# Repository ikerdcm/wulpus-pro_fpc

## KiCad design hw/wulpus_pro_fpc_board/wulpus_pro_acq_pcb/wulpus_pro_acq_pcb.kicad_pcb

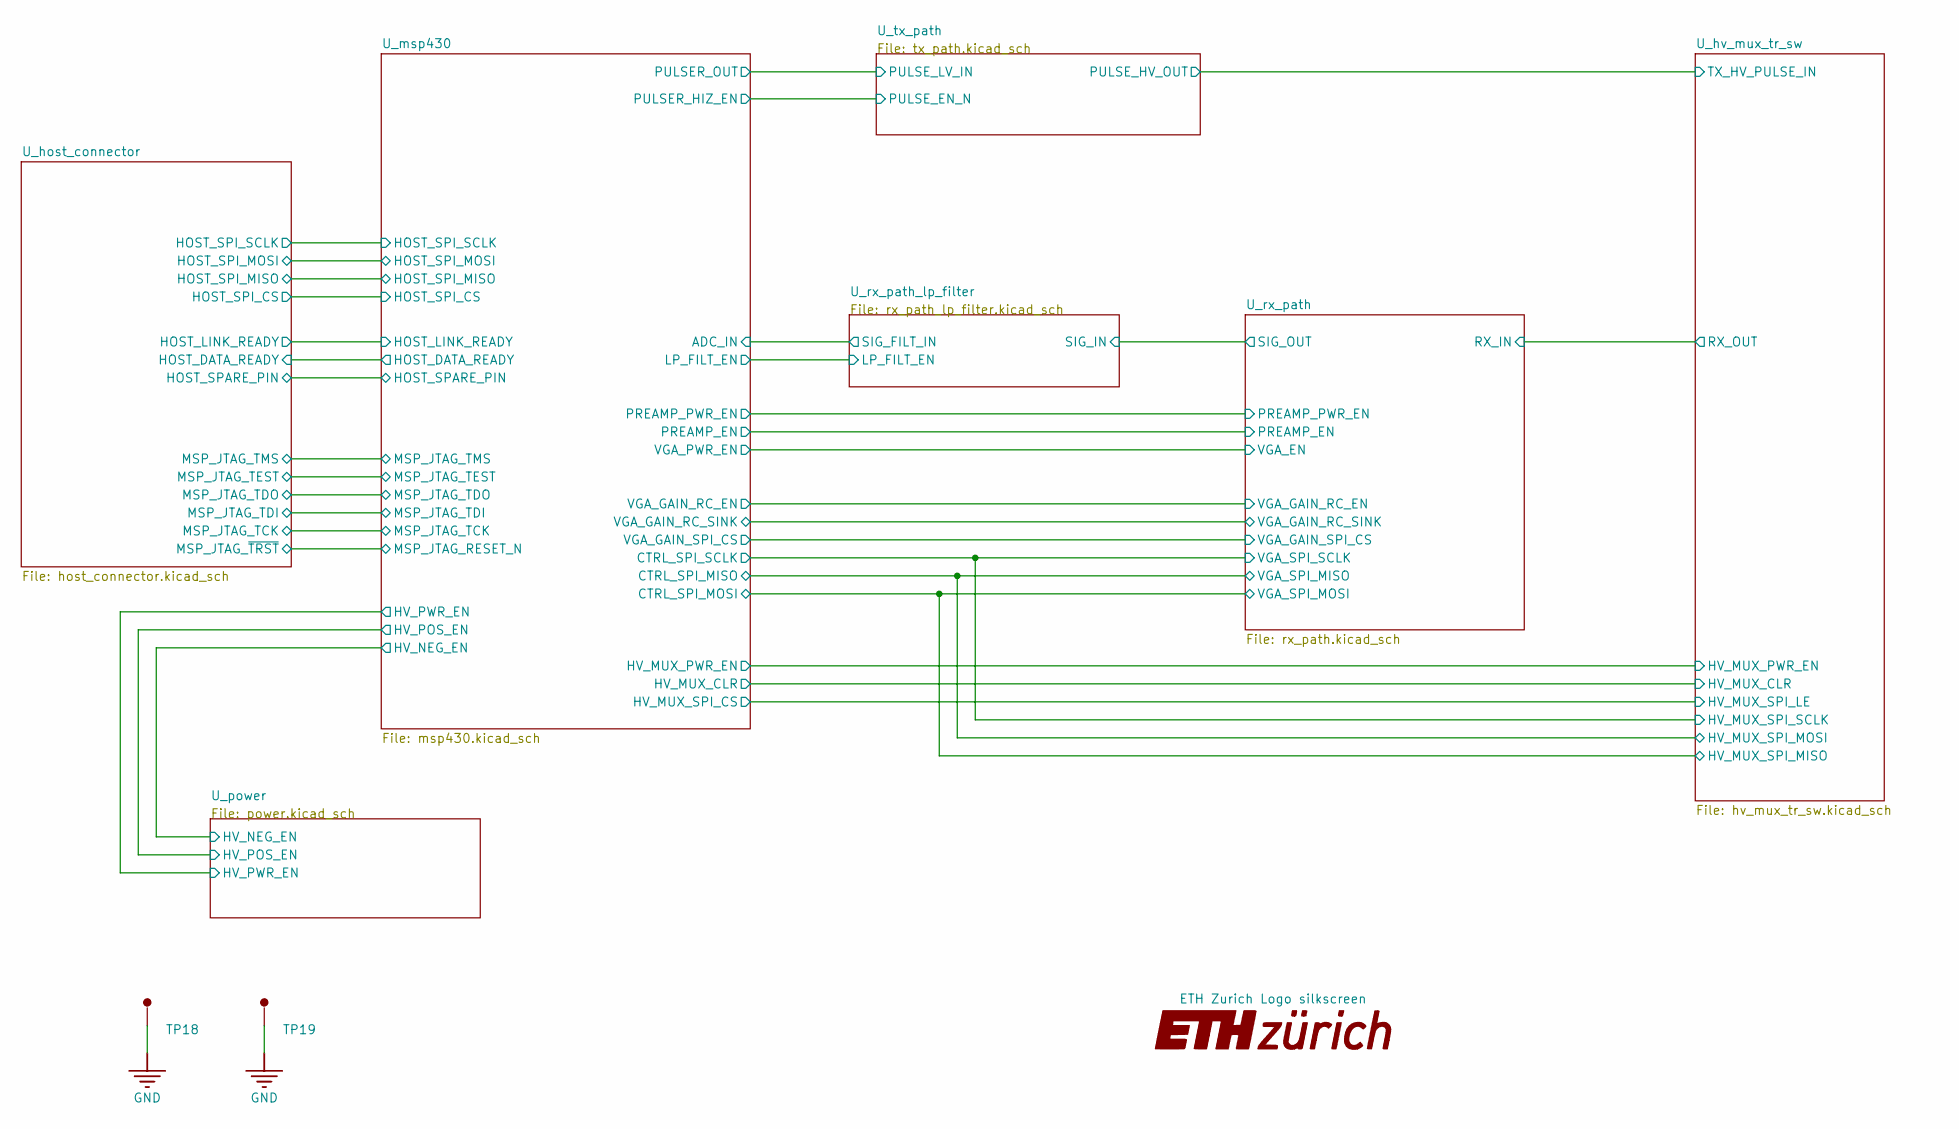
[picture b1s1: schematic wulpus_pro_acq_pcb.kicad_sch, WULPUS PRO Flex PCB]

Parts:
ART1: ETH Zurich Logo silkscreen; ETH_zurich_2mm
TP18, TP19: TP-SM-C-100; TestPoint_Pad_D1.0mm

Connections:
GND: TP18.1 (1_1), TP19.1 (1_1); also elsewhere on the board

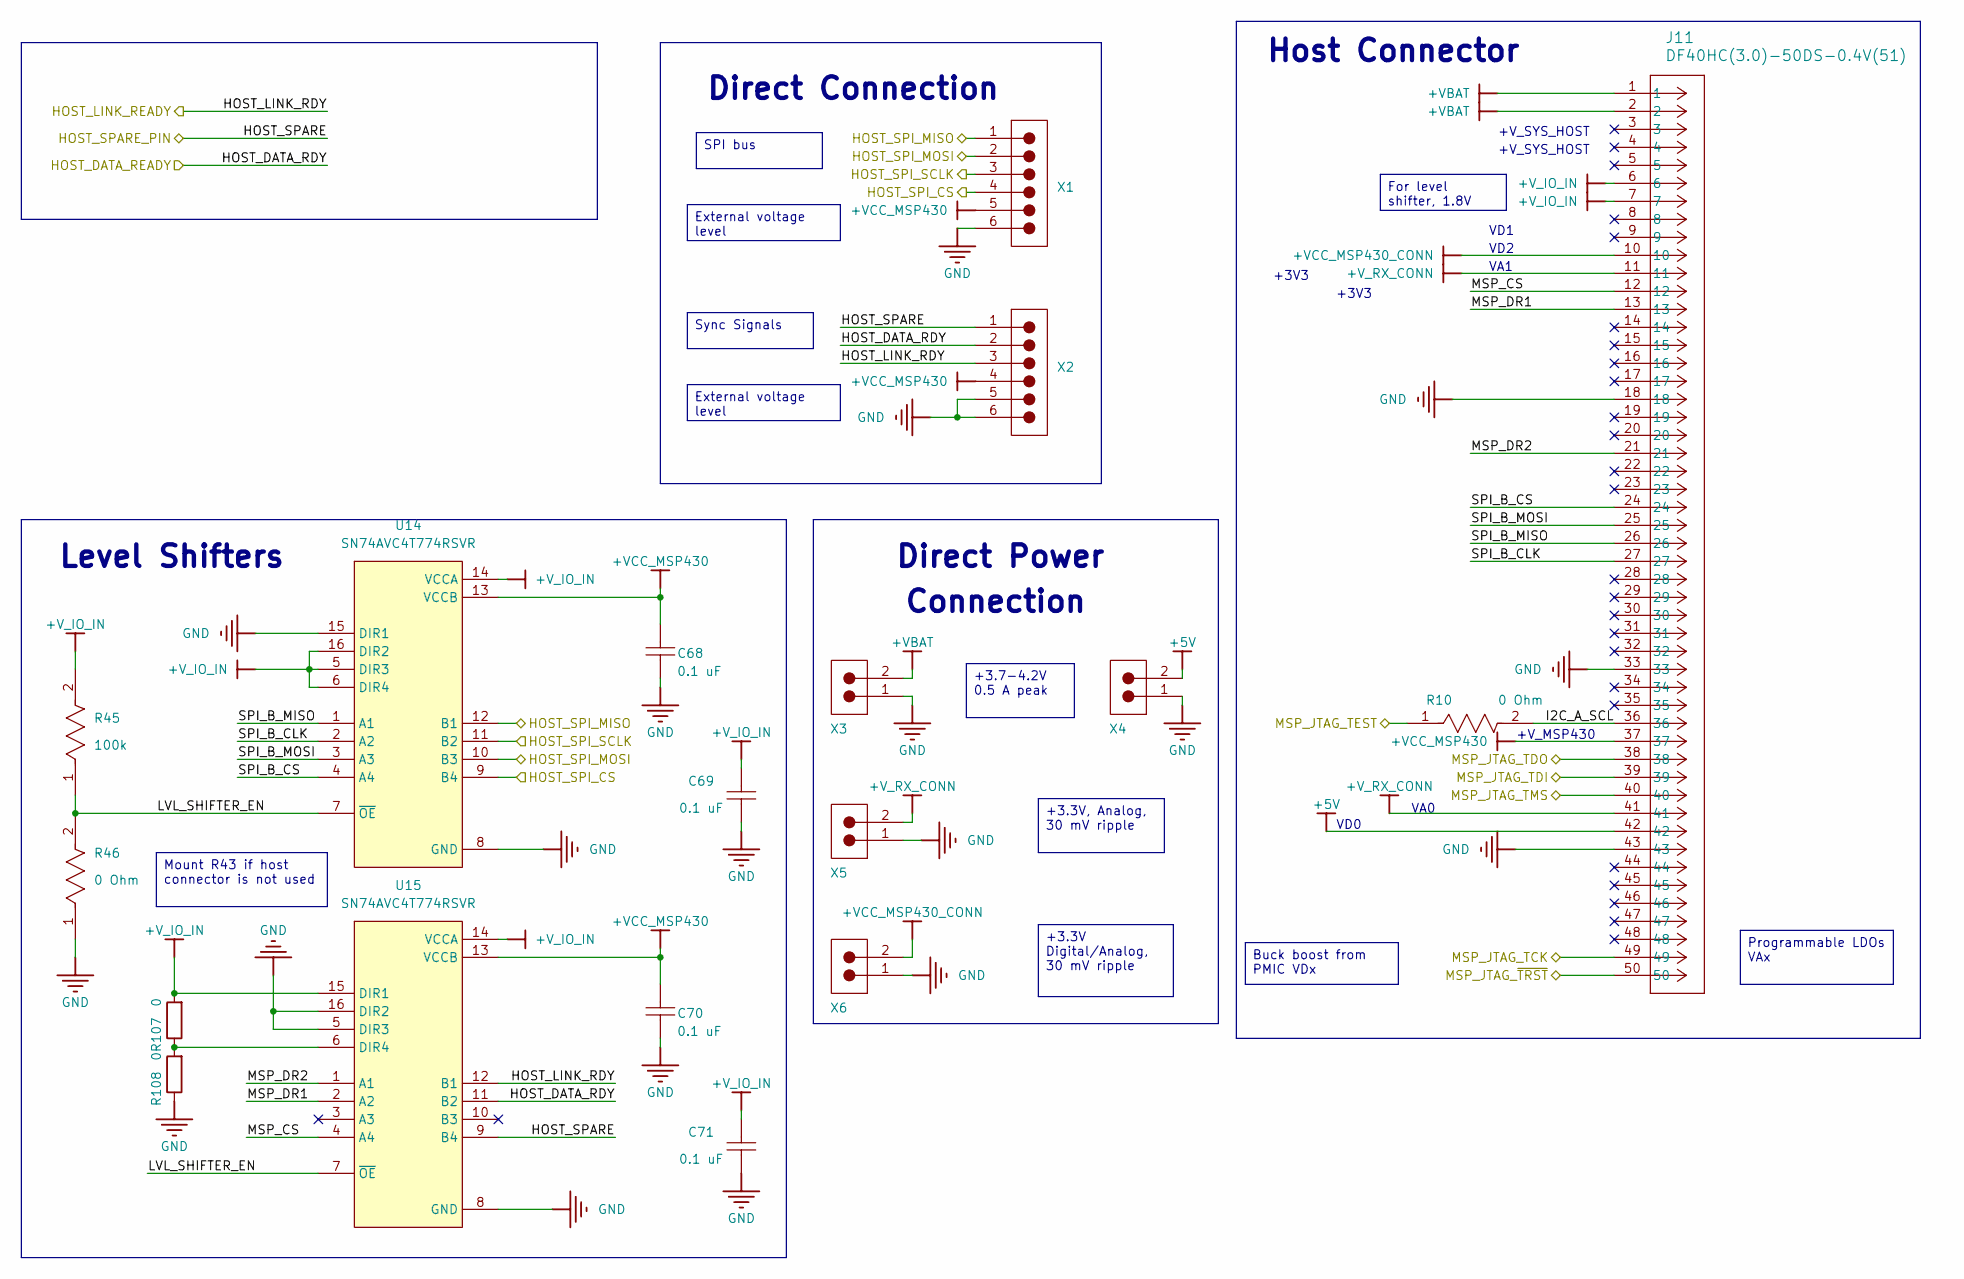
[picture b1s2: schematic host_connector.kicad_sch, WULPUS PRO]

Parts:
C68, C69, C70, C71: 0.1 uF; C_0402_1005Metric; PART NUMBER C0402C104K4RACTU
J11: DF40HC(3.0)-50DS-0.4V(51); CONN_DF40HC3.0-50DS-0.4V51_HIR; MPN DF40HC(3.0)-50DS-0.4V(51); LCSC C3652838
R10, R46: 0 Ohm; R_0402_1005Metric; TOLERANCE 5%; VOLTAGE RATING 50V; MPN CRCW04020000Z0ED
R45: 100k; R_0402_1005Metric; VOLTAGE RATING (DC) 50V; TOLERANCE 1%; MPN ERJ-2RKF1003X
R107, R108: 0; R_0402_1005Metric; Tolerance 5%; MPN ERJ-2GE0R00X; LCSC C17168
U14, U15: SN74AVC4T774RSVR; UQFN-16_1.8x2.6mm_P0.4mm; MPN SN74AVC4T774RSVR; DIGI-KEY_PART_NUMBER 296-24741-1-ND
X1, X2: 68000-106HLF; PinHeader_1x06_P2.54mm_Vertical; CURRENT RATING 3A; VOLTAGE RATING 1.5kV; MPN 68000-102HLF
X3, X4, X5, X6: 68000-102HLF; PinHeader_1x02_P2.54mm_Vertical; CURRENT RATING 3A; FLAMMABILITY RATING UL94 V-0; MANUFACTURER PART NUMBER 68000-102HLF

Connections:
+5V: J11.42, X4.2; also elsewhere on the board
+VBAT: J11.1, J11.2, X3.2; also elsewhere on the board
+VBAT_STM: C68.1, C70.1, J11.37, U14.13 (VCCB), U15.13 (VCCB), X1.5, X2.4; also elsewhere on the board
+VCC_MSP430_CONN: J11.10, X6.2; also elsewhere on the board
+V_IO_IN: C69.1, C71.1, J11.6, J11.7, R45.2, R107.2, U14.5 (DIR3), U14.6 (DIR4), U14.14 (VCCA), U14.16 (DIR2), U15.14 (VCCA), U15.15 (DIR1)
+V_RX_CONN: J11.11, J11.41, X5.2; also elsewhere on the board
/U_host_connector/HOST_DATA_RDY: U15.11 (B2), X2.2; also elsewhere on the board
/U_host_connector/HOST_LINK_RDY: U15.12 (B1), X2.3; also elsewhere on the board
/U_host_connector/HOST_SPARE: U15.9 (B4), X2.1; also elsewhere on the board
/U_host_connector/HOST_SPI_CS: U14.9 (B4), X1.4; also elsewhere on the board
/U_host_connector/HOST_SPI_MISO: U14.12 (B1), X1.1; also elsewhere on the board
/U_host_connector/HOST_SPI_MOSI: U14.10 (B3), X1.2; also elsewhere on the board
/U_host_connector/HOST_SPI_SCLK: U14.11 (B2), X1.3; also elsewhere on the board
/U_host_connector/I2C_A_SCL: J11.36, R10.2
/U_host_connector/LVL_SHIFTER_EN: R45.1, R46.2, U14.7 (~OE), U15.7 (~OE)
/U_host_connector/MSP_CS: J11.12, U15.4 (A4)
/U_host_connector/MSP_DR1: J11.13, U15.2 (A2)
/U_host_connector/MSP_DR2: J11.21, U15.1 (A1)
/U_host_connector/SPI_B_CLK: J11.27, U14.2 (A2)
/U_host_connector/SPI_B_CS: J11.24, U14.4 (A4)
/U_host_connector/SPI_B_MISO: J11.26, U14.1 (A1)
/U_host_connector/SPI_B_MOSI: J11.25, U14.3 (A3)
/U_msp430/MSP_JTAG_RESET_N: J11.50; also elsewhere on the board
/U_msp430/MSP_JTAG_TCK: J11.49; also elsewhere on the board
/U_msp430/MSP_JTAG_TDI: J11.39; also elsewhere on the board
/U_msp430/MSP_JTAG_TDO: J11.38; also elsewhere on the board
/U_msp430/MSP_JTAG_TEST: R10.1; also elsewhere on the board
/U_msp430/MSP_JTAG_TMS: J11.40; also elsewhere on the board
GND: C68.2, C69.2, C70.2, C71.2, J11.18, J11.33, J11.43, R46.1, R108.1, U14.8 (GND), U14.15 (DIR1), U15.5 (DIR3), U15.8 (GND), U15.16 (DIR2), X1.6, X2.5, X2.6, X3.1, X4.1, X5.1, X6.1; also elsewhere on the board
unnamed: R107.1, R108.2, U15.6 (DIR4)

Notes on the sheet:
+V_SYS_HOST
Connection
Direct Connection
Direct Power
VD1
+V_MSP430
+3V3
Level Shifters
VA1
VD0
VD2
Host Connector
VA0
+3.3V Digital/Analog, 30 mV ripple
Mount R43 if host connector is not used
+3.3V, Analog, 30 mV ripple
Sync Signals
SPI bus
+3.7-4.2V 0.5 A peak
External voltage level
For level shifter, 1.8V
Programmable LDOs VAx
Buck boost from PMIC VDx

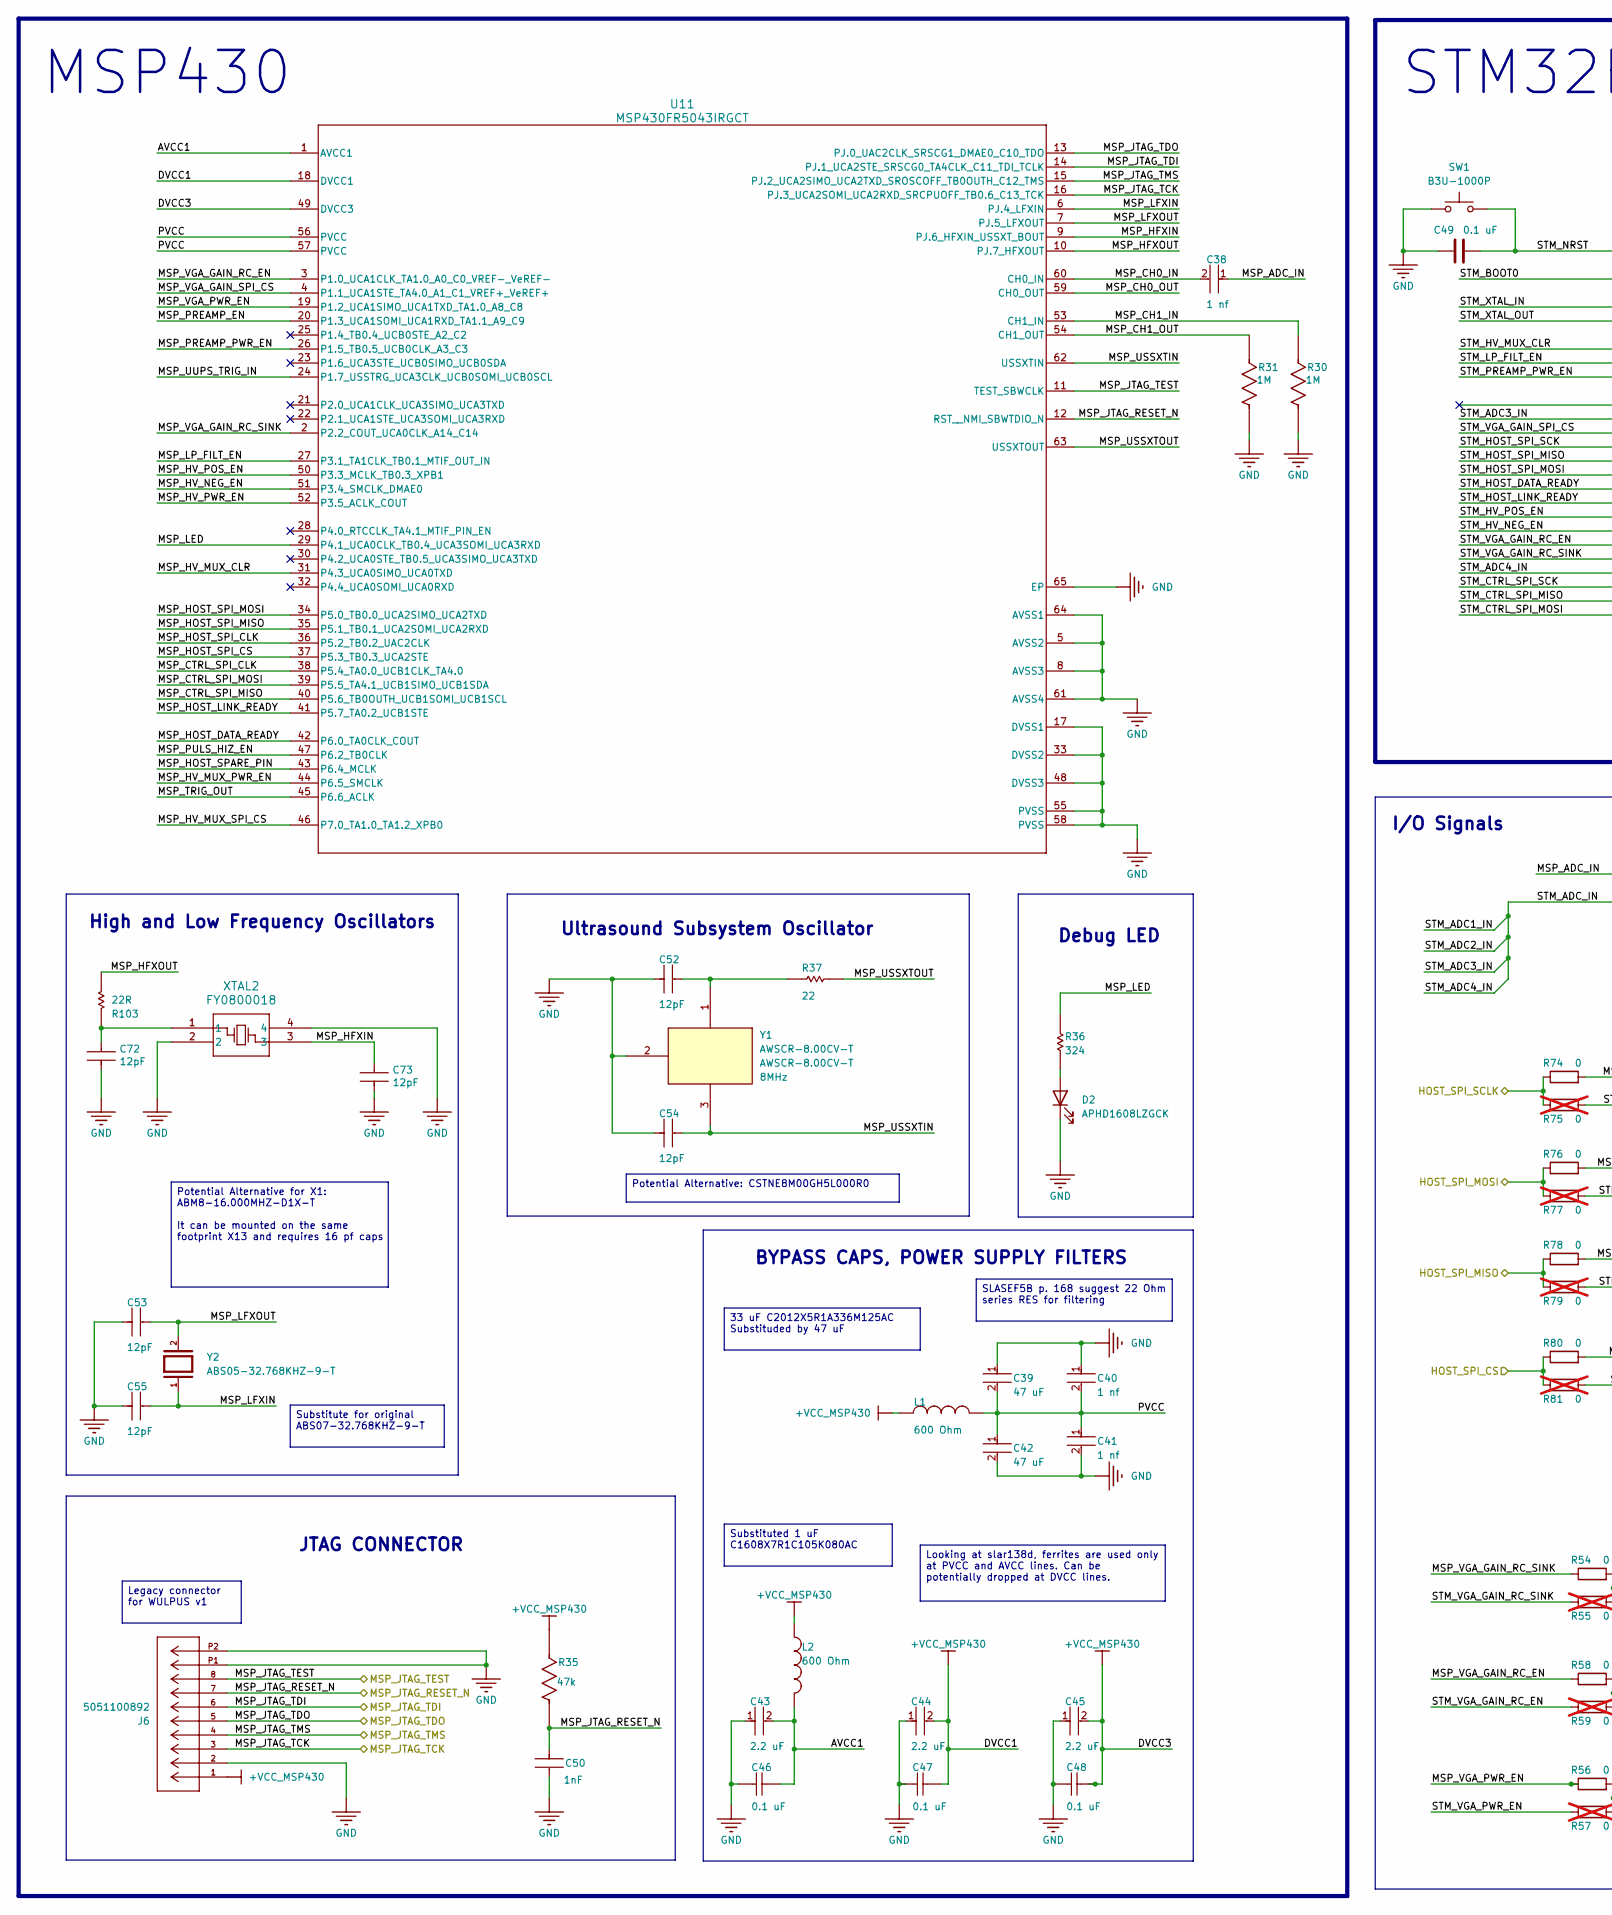
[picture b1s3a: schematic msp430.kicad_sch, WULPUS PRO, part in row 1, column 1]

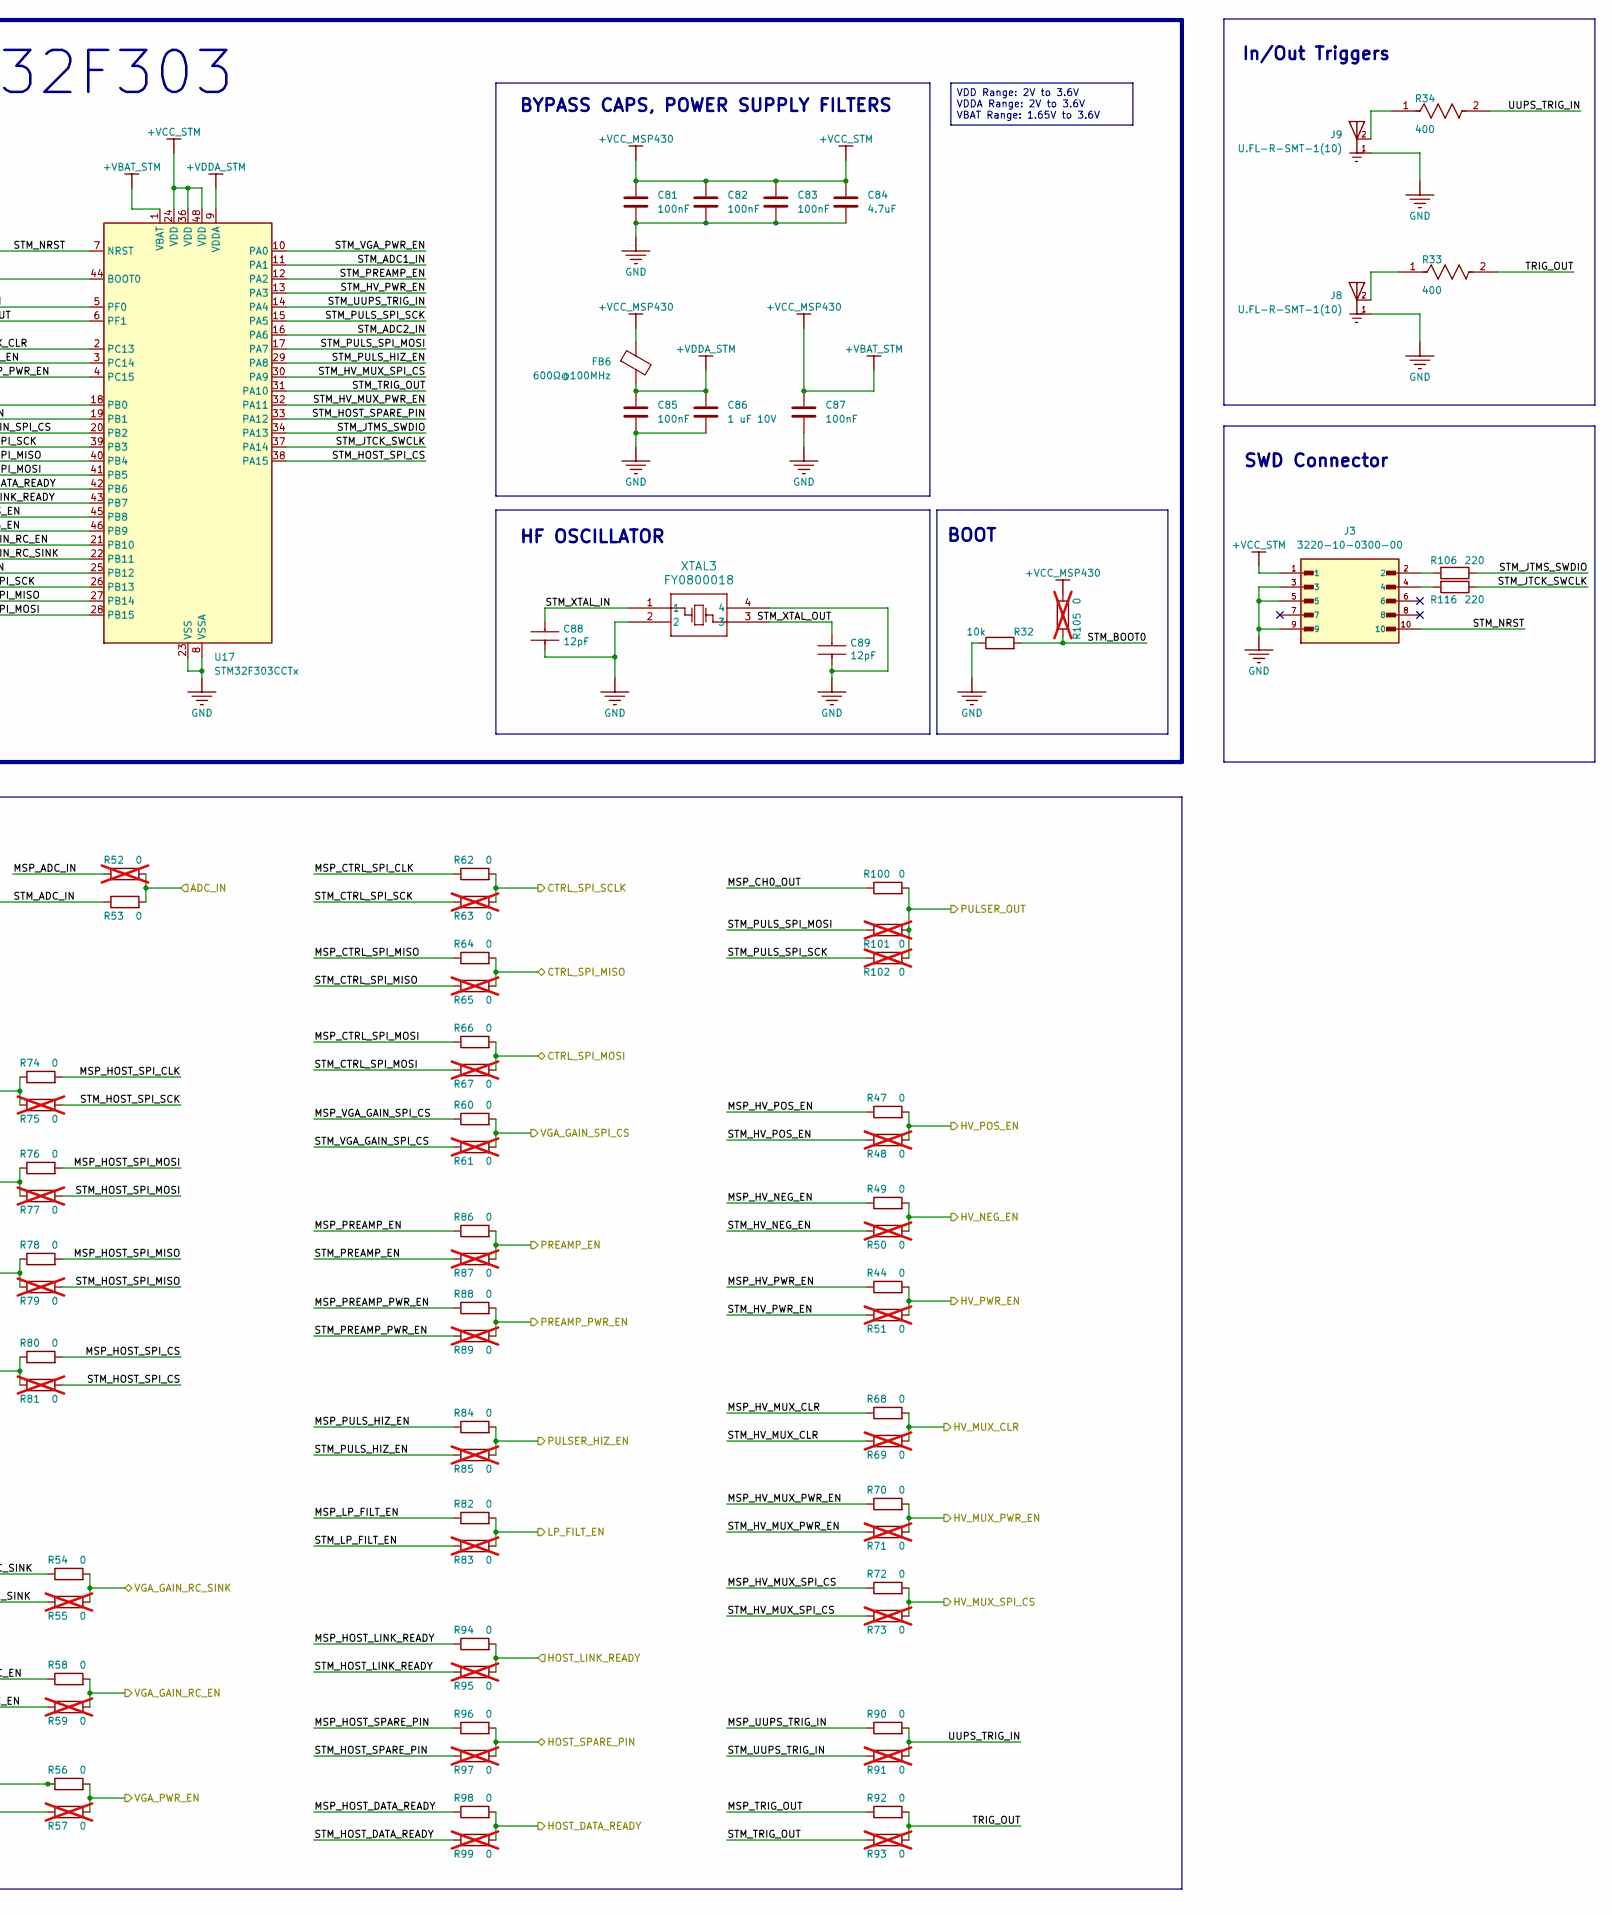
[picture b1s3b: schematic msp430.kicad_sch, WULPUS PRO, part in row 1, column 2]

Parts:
C38, C40, C41: 1 nf; C_0402_1005Metric; TOLERANCE 5%; VOLTAGE RATING 50V; PART NUMBER GRM1555C1H102JA01D
C39, C42: 47 uF; C_0603_1608Metric; TOLERANCE 20%; VOLTAGE RATING (DC) 6.3V; PART NUMBER GRM188R60J476ME01D
C43, C44, C45: 2.2 uF; C_0402_1005Metric; VOLTAGE RATING 10V; VOLTAGE RATING (DC) 10V; PART NUMBER C1005X7S1A225K050BC
C46, C47, C48: 0.1 uF; C_0402_1005Metric; PART NUMBER C0402C104K4RACTU
C49: 0.1 uF; C_0402_1005Metric; MPN C0402C104K4RACTU
C50: 1000 pF 50V; C_0402_1005Metric; TOLERANCE 5%; VOLTAGE RATING 50V; PART NUMBER GRM1555C1H102JA01D
C52, C53, C54, C55, C72, C73, C88, C89: 12 pF 50V; C_0402_1005Metric; TOLERANCE 2%; VOLTAGE RATING 50V; PART NUMBER GJM1555C1H120GB01D
C81, C82, C83, C85, C87: 100nF; C_0402_1005Metric; MPN C0402C104K4RACTU
C84: 4.7uF; C_0402_1005Metric; MPN MLASL105BB5475MFNB33
C86: 1 uF 10V; C_0402_1005Metric; MPN GRM155Z71A105KE01D
D2: APHD1608LZGCK; LED_0603_1608Metric; MPN APHD1608LZGCK
FB6: 600Ω@100MHz; L_0603_1608Metric; MPN BLM18AG601SZ1; LCSC C710353
J3: 3220-10-0300-00; CNC_3220-10-0300-00; PARTREV D; LCSC C7501307
J6: 5051100892; CON_5051100892_MOL; MPN 5051100892; LCSC C5902847
J8, J9: U.FL-R-SMT-1(10); HRS_U.FL-R-SMT-1_10_; MPN U.FL-R-SMT-1(10); DigiKey_Part_Number H11891CT-ND
L1, L2: 742792040; L_0805_2012Metric_Pad1.05x1.20mm_HandSolder; MPN 742792040
R30, R31: CRCW04021M00FKED; R_0402_1005Metric; POWER RATING 63mW; VOLTAGE RATING (DC) 50V; MPN CRCW04021M00FKED
R32: 10k; R_0402_1005Metric
R33, R34: 400; R_0402_1005Metric; TOLERANCE 1%; VOLTAGE RATING 50V; MPN CRCW04021R00FKEDC
R35: CRCW040247K0FKED; R_0402_1005Metric; TOLERANCE 1%; VOLTAGE RATING (DC) 50V; MPN CRCW040247K0FKED
R36: 324R; R_0402_1005Metric; PART NUMBER CPF0402B324RE1
R37, R103: 22R; R_0402_1005Metric; PART NUMBER RC0402JR-0722RL
R44, R47, R49, R53, R54, R56, R58, R60, R62, R64, R66, R68, R70, R72, R74, R76, R78, R80, R82, R84, R86, R88, R90, R92, R94, R96, R98, R100: 0; R_0402_1005Metric; Tolerance 5%; MPN ERJ-2GE0R00X; LCSC C17168
R48, R50, R51, R52, R55, R57, R59, R61, R63, R65, R67, R69, R71, R73, R75, R77, R79, R81, R83, R85, R87, R89, R91, R93, R95, R97, R99, R101, R102, R105: 0; R_0402_1005Metric; Tolerance 5%; MPN ERJ-2GE0R00X; LCSC C17168; not fitted
R106, R116: 220; R_0402_1005Metric; Tolerance 1%; MPN ERJ-2RKF2200X; LCSC C413071
SW1: Button Switch SPST-No; SW_SPST_B3U-1000P; MPN B3U-1000P; LCSC C231329
U11: MSP430FR5043IRGCT; VQFN-64-1EP_9x9mm_P0.5mm_EP5.4x5.4mm; MPN MSP430FR5043IRGCT
U17: STM32F303CCTx; LQFP-48_7x7mm_P0.5mm; MPN STM32F303CCTx
XTAL2, XTAL3: FY0800018; 4xtal- 1-3xtal 2-4NC_DIO; MPN FY0800018; LCSC C6951614
Y1: AWSCR-8.00CV-T; AWSCR-8.00CV-T_ABR; MPN AWSCR-8.00CV-T; LCSC C2650764
Y2: ABS05-32.768KHZ-9-T; XTAL_ABS05-32.768KHZ-9-T; PARTREV 11/3/2021; DigiKey_Part_Number 535-ABS05-32.768KHZ-9-TCT-ND

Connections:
+VBAT_STM: C44.2, C45.2, C47.1, C48.1, C81.1, C82.1, C83.1, C84.1, C87.1, FB6.1, J3.1, J6.1, L1.1, L2.1, R35.1, R105.2, U11.18 (DVCC1), U11.49 (DVCC3), U17.1 (VBAT), U17.24 (VDD), U17.36 (VDD), U17.48 (VDD); also elsewhere on the board
+VDDA_STM: C85.1, C86.1, FB6.2, U17.9 (VDDA)
/U_host_connector/HOST_DATA_RDY: R98.2, R99.2; also elsewhere on the board
/U_host_connector/HOST_LINK_RDY: R94.2, R95.2; also elsewhere on the board
/U_host_connector/HOST_SPARE: R96.2, R97.2; also elsewhere on the board
/U_host_connector/HOST_SPI_CS: R80.1, R81.1; also elsewhere on the board
/U_host_connector/HOST_SPI_MISO: R78.1, R79.1; also elsewhere on the board
/U_host_connector/HOST_SPI_MOSI: R76.1, R77.1; also elsewhere on the board
/U_host_connector/HOST_SPI_SCLK: R74.1, R75.1; also elsewhere on the board
/U_hv_mux_tr_sw/HV_MUX_CLR: R68.2, R69.2; also elsewhere on the board
/U_hv_mux_tr_sw/HV_MUX_PWR_EN: R70.2, R71.2; also elsewhere on the board
/U_hv_mux_tr_sw/HV_MUX_SPI_LE: R72.2, R73.2; also elsewhere on the board
/U_hv_mux_tr_sw/HV_MUX_SPI_MISO: R66.2, R67.2; also elsewhere on the board
/U_hv_mux_tr_sw/HV_MUX_SPI_MOSI: R64.2, R65.2; also elsewhere on the board
/U_hv_mux_tr_sw/HV_MUX_SPI_SCLK: R62.2, R63.2; also elsewhere on the board
/U_msp430/ADC_IN: R52.2, R53.2; also elsewhere on the board
/U_msp430/AVCC1: C43.2, C46.1, L2.2, U11.1 (AVCC1)
/U_msp430/HV_PWR_EN: R44.2, R51.2; also elsewhere on the board
/U_msp430/MSP_ADC_IN: C38.1, R52.1
/U_msp430/MSP_CH0_IN: C38.2, U11.60 (CH0_IN)
/U_msp430/MSP_CH0_OUT: R100.1, U11.59 (CH0_OUT)
/U_msp430/MSP_CH1_IN: R30.1, U11.53 (CH1_IN)
/U_msp430/MSP_CH1_OUT: R31.1, U11.54 (CH1_OUT)
/U_msp430/MSP_CTRL_SPI_CLK: R62.1, U11.38 (P5.4_TA0.0_UCB1CLK_TA4.0)
/U_msp430/MSP_CTRL_SPI_MISO: R64.1, U11.40 (P5.6_TB0OUTH_UCB1SOMI_UCB1SCL)
/U_msp430/MSP_CTRL_SPI_MOSI: R66.1, U11.39 (P5.5_TA4.1_UCB1SIMO_UCB1SDA)
/U_msp430/MSP_HFXIN: C73.2, U11.9 (PJ.6_HFXIN_USSXT_BOUT), XTAL2.3
/U_msp430/MSP_HFXOUT: R103.2, U11.10 (PJ.7_HFXOUT)
/U_msp430/MSP_HOST_DATA_READY: R98.1, U11.42 (P6.0_TA0CLK_COUT)
/U_msp430/MSP_HOST_LINK_READY: R94.1, U11.41 (P5.7_TA0.2_UCB1STE)
/U_msp430/MSP_HOST_SPARE_PIN: R96.1, U11.43 (P6.4_MCLK)
/U_msp430/MSP_HOST_SPI_CLK: R74.2, U11.36 (P5.2_TB0.2_UAC2CLK)
/U_msp430/MSP_HOST_SPI_CS: R80.2, U11.37 (P5.3_TB0.3_UCA2STE)
/U_msp430/MSP_HOST_SPI_MISO: R78.2, U11.35 (P5.1_TB0.1_UCA2SOMI_UCA2RXD)
/U_msp430/MSP_HOST_SPI_MOSI: R76.2, U11.34 (P5.0_TB0.0_UCA2SIMO_UCA2TXD)
/U_msp430/MSP_HV_MUX_CLR: R68.1, U11.31 (P4.3_UCA0SIMO_UCA0TXD)
/U_msp430/MSP_HV_MUX_PWR_EN: R70.1, U11.44 (P6.5_SMCLK)
/U_msp430/MSP_HV_MUX_SPI_CS: R72.1, U11.46 (P7.0_TA1.0_TA1.2_XPB0)
/U_msp430/MSP_HV_NEG_EN: R49.1, U11.51 (P3.4_SMCLK_DMAE0)
/U_msp430/MSP_HV_POS_EN: R47.1, U11.50 (P3.3_MCLK_TB0.3_XPB1)
/U_msp430/MSP_HV_PWR_EN: R44.1, U11.52 (P3.5_ACLK_COUT)
/U_msp430/MSP_JTAG_RESET_N: C50.1, J6.7, R35.2, U11.12 (RST__NMI_SBWTDIO_N); also elsewhere on the board
/U_msp430/MSP_JTAG_TCK: J6.3, U11.16 (PJ.3_UCA2SOMI_UCA2RXD_SRCPUOFF_TB0.6_C1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); also elsewhere on the board
/U_msp430/MSP_JTAG_TDI: J6.6, U11.14 (PJ.1_UCA2STE_SRSCG0_TA4CLK_C11_TDI_TCLK); also elsewhere on the board
/U_msp430/MSP_JTAG_TDO: J6.5, U11.13 (PJ.0_UAC2CLK_SRSCG1_DMAE0_C10_TDO); also elsewhere on the board
/U_msp430/MSP_JTAG_TEST: J6.8, U11.11 (TEST_SBWCLK); also elsewhere on the board
/U_msp430/MSP_JTAG_TMS: J6.4, U11.15 (PJ.2_UCA2SIMO_UCA2TXD_SROSCOFF_TB0OUTH_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); also elsewhere on the board
/U_msp430/MSP_LED: R36.1, U11.29 (P4.1_UCA0CLK_TB0.4_UCA3SOMI_UCA3RXD)
/U_msp430/MSP_LFXIN: C55.2, U11.6 (PJ.4_LFXIN), Y2.1
/U_msp430/MSP_LFXOUT: C53.2, U11.7 (PJ.5_LFXOUT), Y2.2
/U_msp430/MSP_LP_FILT_EN: R82.1, U11.27 (P3.1_TA1CLK_TB0.1_MTIF_OUT_IN)
/U_msp430/MSP_PREAMP_EN: R86.1, U11.20 (P1.3_UCA1SOMI_UCA1RXD_TA1.1_A9_C9)
/U_msp430/MSP_PREAMP_PWR_EN: R88.1, U11.26 (P1.5_TB0.5_UCB0CLK_A3_C3)
/U_msp430/MSP_PULS_HIZ_EN: R84.1, U11.47 (P6.2_TB0CLK)
/U_msp430/MSP_TRIG_OUT: R92.1, U11.45 (P6.6_ACLK)
/U_msp430/MSP_USSXTIN: C54.2, U11.62 (USSXTIN), Y1.3
/U_msp430/MSP_USSXTOUT: R37.2, U11.63 (USSXTOUT)
/U_msp430/MSP_UUPS_TRIG_IN: R90.1, U11.24 (P1.7_USSTRG_UCA3CLK_UCB0SOMI_UCB0SCL)
/U_msp430/MSP_VGA_GAIN_RC_EN: R58.1, U11.3 (P1.0_UCA1CLK_TA1.0_A0_C0_VREF-_VeREF-)
/U_msp430/MSP_VGA_GAIN_RC_SINK: R54.1, U11.2 (P2.2_COUT_UCA0CLK_A14_C14)
/U_msp430/MSP_VGA_GAIN_SPI_CS: R60.1, U11.4 (P1.1_UCA1STE_TA4.0_A1_C1_VREF+_VeREF+)
/U_msp430/MSP_VGA_PWR_EN: R56.1, U11.19 (P1.2_UCA1SIMO_UCA1TXD_TA1.0_A8_C8)
/U_msp430/PREAMP_PWR_EN: R88.2, R89.2; also elsewhere on the board
/U_msp430/PULSER_HIZ_EN: R84.2, R85.2; also elsewhere on the board
/U_msp430/PULSER_OUT: R100.2, R101.2, R102.2; also elsewhere on the board
/U_msp430/PVCC: C39.2, C40.2, C41.1, C42.1, L1.2, U11.56 (PVCC), U11.57 (PVCC)
/U_msp430/STM_BOOT0: R32.2, R105.1, U17.44 (BOOT0)
/U_msp430/STM_CTRL_SPI_MISO: R65.1, U17.27 (PB14)
/U_msp430/STM_CTRL_SPI_MOSI: R67.1, U17.28 (PB15)
/U_msp430/STM_CTRL_SPI_SCK: R63.1, U17.26 (PB13)
/U_msp430/STM_HOST_DATA_READY: R99.1, U17.42 (PB6)
/U_msp430/STM_HOST_LINK_READY: R95.1, U17.43 (PB7)
/U_msp430/STM_HOST_SPARE_PIN: R97.1, U17.33 (PA12)
/U_msp430/STM_HOST_SPI_CS: R81.2, U17.38 (PA15)
/U_msp430/STM_HOST_SPI_MISO: R79.2, U17.40 (PB4)
/U_msp430/STM_HOST_SPI_MOSI: R77.2, U17.41 (PB5)
/U_msp430/STM_HOST_SPI_SCK: R75.2, U17.39 (PB3)
/U_msp430/STM_HV_MUX_CLR: R69.1, U17.2 (PC13)
/U_msp430/STM_HV_MUX_PWR_EN: R71.1, U17.32 (PA11)
/U_msp430/STM_HV_MUX_SPI_CS: R73.1, U17.30 (PA9)
/U_msp430/STM_HV_NEG_EN: R50.1, U17.46 (PB9)
/U_msp430/STM_HV_POS_EN: R48.1, U17.45 (PB8)
/U_msp430/STM_HV_PWR_EN: R51.1, U17.13 (PA3)
/U_msp430/STM_JTCK_SWCLK: R116.1, U17.37 (PA14)
/U_msp430/STM_JTMS_SWDIO: R106.1, U17.34 (PA13)
/U_msp430/STM_LP_FILT_EN: R83.1, U17.3 (PC14)
/U_msp430/STM_NRST: C49.1, J3.10, SW1.2, U17.7 (NRST)
/U_msp430/STM_PREAMP_EN: R87.1, U17.12 (PA2)
/U_msp430/STM_PREAMP_PWR_EN: R89.1, U17.4 (PC15)
/U_msp430/STM_PULS_HIZ_EN: R85.1, U17.29 (PA8)
/U_msp430/STM_PULS_SPI_MOSI: R101.1, U17.17 (PA7)
/U_msp430/STM_PULS_SPI_SCK: R102.1, U17.15 (PA5)
/U_msp430/STM_TRIG_OUT: R93.1, U17.31 (PA10)
/U_msp430/STM_UUPS_TRIG_IN: R91.1, U17.14 (PA4)
/U_msp430/STM_VGA_GAIN_RC_EN: R59.1, U17.21 (PB10)
/U_msp430/STM_VGA_GAIN_RC_SINK: R55.1, U17.22 (PB11)
/U_msp430/STM_VGA_GAIN_SPI_CS: R61.1, U17.20 (PB2)
/U_msp430/STM_VGA_PWR_EN: R57.1, U17.10 (PA0)
/U_msp430/STM_XTAL_IN: C88.2, U17.5 (PF0), XTAL3.1
/U_msp430/STM_XTAL_OUT: C89.2, U17.6 (PF1), XTAL3.3
/U_msp430/TRIG_OUT: R33.2, R92.2, R93.2
/U_msp430/UUPS_TRIG_IN: R34.2, R90.2, R91.2
/U_msp430/VGA_GAIN_RC_EN: R58.2, R59.2; also elsewhere on the board
/U_msp430/VGA_GAIN_RC_SINK: R54.2, R55.2; also elsewhere on the board
/U_msp430/VGA_GAIN_SPI_CS: R60.2, R61.2; also elsewhere on the board
/U_msp430/VGA_PWR_EN: R56.2, R57.2; also elsewhere on the board
/U_power/HV_EN1: R47.2, R48.2; also elsewhere on the board
/U_power/HV_EN2: R49.2, R50.2; also elsewhere on the board
/U_rx_path/PREAMP_SHDN_N: R86.2, R87.2; also elsewhere on the board
/U_rx_path_lp_filter/FILTER_SHDN_N: R82.2, R83.2; also elsewhere on the board
GND: C39.1, C40.1, C41.2, C42.2, C43.1, C44.1, C45.1, C46.2, C47.2, C48.2, C49.2, C50.2, C52.1, C53.1, C54.1, C55.1, C72.1, C73.1, C81.2, C82.2, C83.2, C84.2, C85.2, C86.2, C87.2, C88.1, C89.1, D2.1 (K), J3.3, J3.5, J3.9, J6.2, J6.P1, J6.P2, J8.1, J8.3, J9.1, J9.3, R30.2, R31.2, R32.1, SW1.1, U11.5 (AVSS2), U11.8 (AVSS3), U11.17 (DVSS1), U11.33 (DVSS2), U11.48 (DVSS3), U11.55 (PVSS), U11.58 (PVSS), U11.61 (AVSS4), U11.64 (AVSS1), U11.65 (EP), U17.8 (VSSA), U17.23 (VSS), U17.35 (VSS), U17.47 (VSS), XTAL2.2, XTAL2.4, XTAL3.2, XTAL3.4, Y1.2; also elsewhere on the board
unnamed: C52.2, R37.1, Y1.1
unnamed: C72.2, R103.1, XTAL2.1
unnamed: D2.2 (A), R36.2
unnamed: J3.2, R106.2
unnamed: J3.4, R116.2
unnamed: J8.2, R33.1
unnamed: J9.2, R34.1

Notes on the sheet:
High and Low Frequency Oscillators
BYPASS CAPS, POWER SUPPLY FILTERS
Debug LED
HF OSCILLATOR
MSP430
BOOT
SWD Connector
In/Out Triggers
STM32F303
JTAG CONNECTOR
Ultrasound Subsystem Oscillator
I/O Signals
VDD Range: 2V to 3.6V VDDA Range: 2V to 3.6V VBAT Range: 1.65V to 3.6V
Looking at slar138d, ferrites are used only at PVCC and AVCC lines. Can be potentially dropped at DVCC lines.
Substituted 1 uF C1608X7R1C105K080AC
33 uF C2012X5R1A336M125AC Substituded by 47 uF
SLASEF5B p. 168 suggest 22 Ohm series RES for filtering
Substitute for original ABS07-32.768KHZ-9-T
Potential Alternative for X1: ABM8-16.000MHZ-D1X-T It can be mounted on the same footprint X13 and requires 16 pf caps
Legacy connector for WULPUS v1
Potential Alternative: CSTNE8M00GH5L000R0

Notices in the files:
parts and their libraries:
COPYRIGHT: Copyright (C) 2021 Ultra Librarian. All rights reserved.
